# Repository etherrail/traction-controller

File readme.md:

# EtherRail Traction Controller TC1000PX22+D+EA
The WiFi based controller for locomotives and other rolling stock.
This device is a drop in replacement for any DCC boards.

Main Features
- WiFi enabled
- Plux2 Interface according to [NEM 658](./documentation/nem658.pdf)
- Inertia Sensor for speed control (instead of the common power control)
- Sound up to 96kHz
- 1A motor current (3.6A Peak)
- Track power probe
- Low production cost
- Tip over, stall and push detection

Product Code
- `TC` traction controller
- `1000` 1000mA nominal current
- `PX22` PluX22 plugging interface (NEM 658)
- `+D` debugging version (USB compatible, status LEDs)
- `+CA` external antenna

## To Do
- Test Boards (currently in production)
- Add GPIO pins

## Connectivity
The device connects with WiFi or Bluetooth.
An external antenna should be attached.

## Ineria Sensor
Usually, the trains are controlled by setting a motor power level, not a target speed. The IMU sensor integrates an accelerometer and a gyroscope, which can be used to estimate the actual speed of the train.

No more speed calibrations and motor ramps - the controller can automatically compensate for heavier trains or gradients. Stalling can be detect too, both total stalling and wheel-slip, which can then be counter acted with automatically induced power bursts. The controller can detect being pushed too, for example in a collision case. And even a tip over can be detected.

## Track Power Probe
The traction controller constantly measures the track voltage.
When an outage is detected (which usually happens every couple miliseconds, even with clean tracks), the controller goes into sleep mode to preserve energy on the on board capacitor bank.

This can be used to monitor the tracks quality and schedule maintenance before issues arise.

## Sound
The board contains a 3.2W@4Ohm sound chip.

To be tested.

## Function Outputs
600mA per channel.

Warning: The output are directly connected to the P-Channel mosfets, additional protected may be required for some output devices.

## Expandability
The processor used on this device (ESP32C3) is more than capable for this task.
We could add camera functionality with this chip!
DCC emulation is theoretically possible.

The board currently contains a full USB debugging interface (pads only, but a programmer is included on the ESP).

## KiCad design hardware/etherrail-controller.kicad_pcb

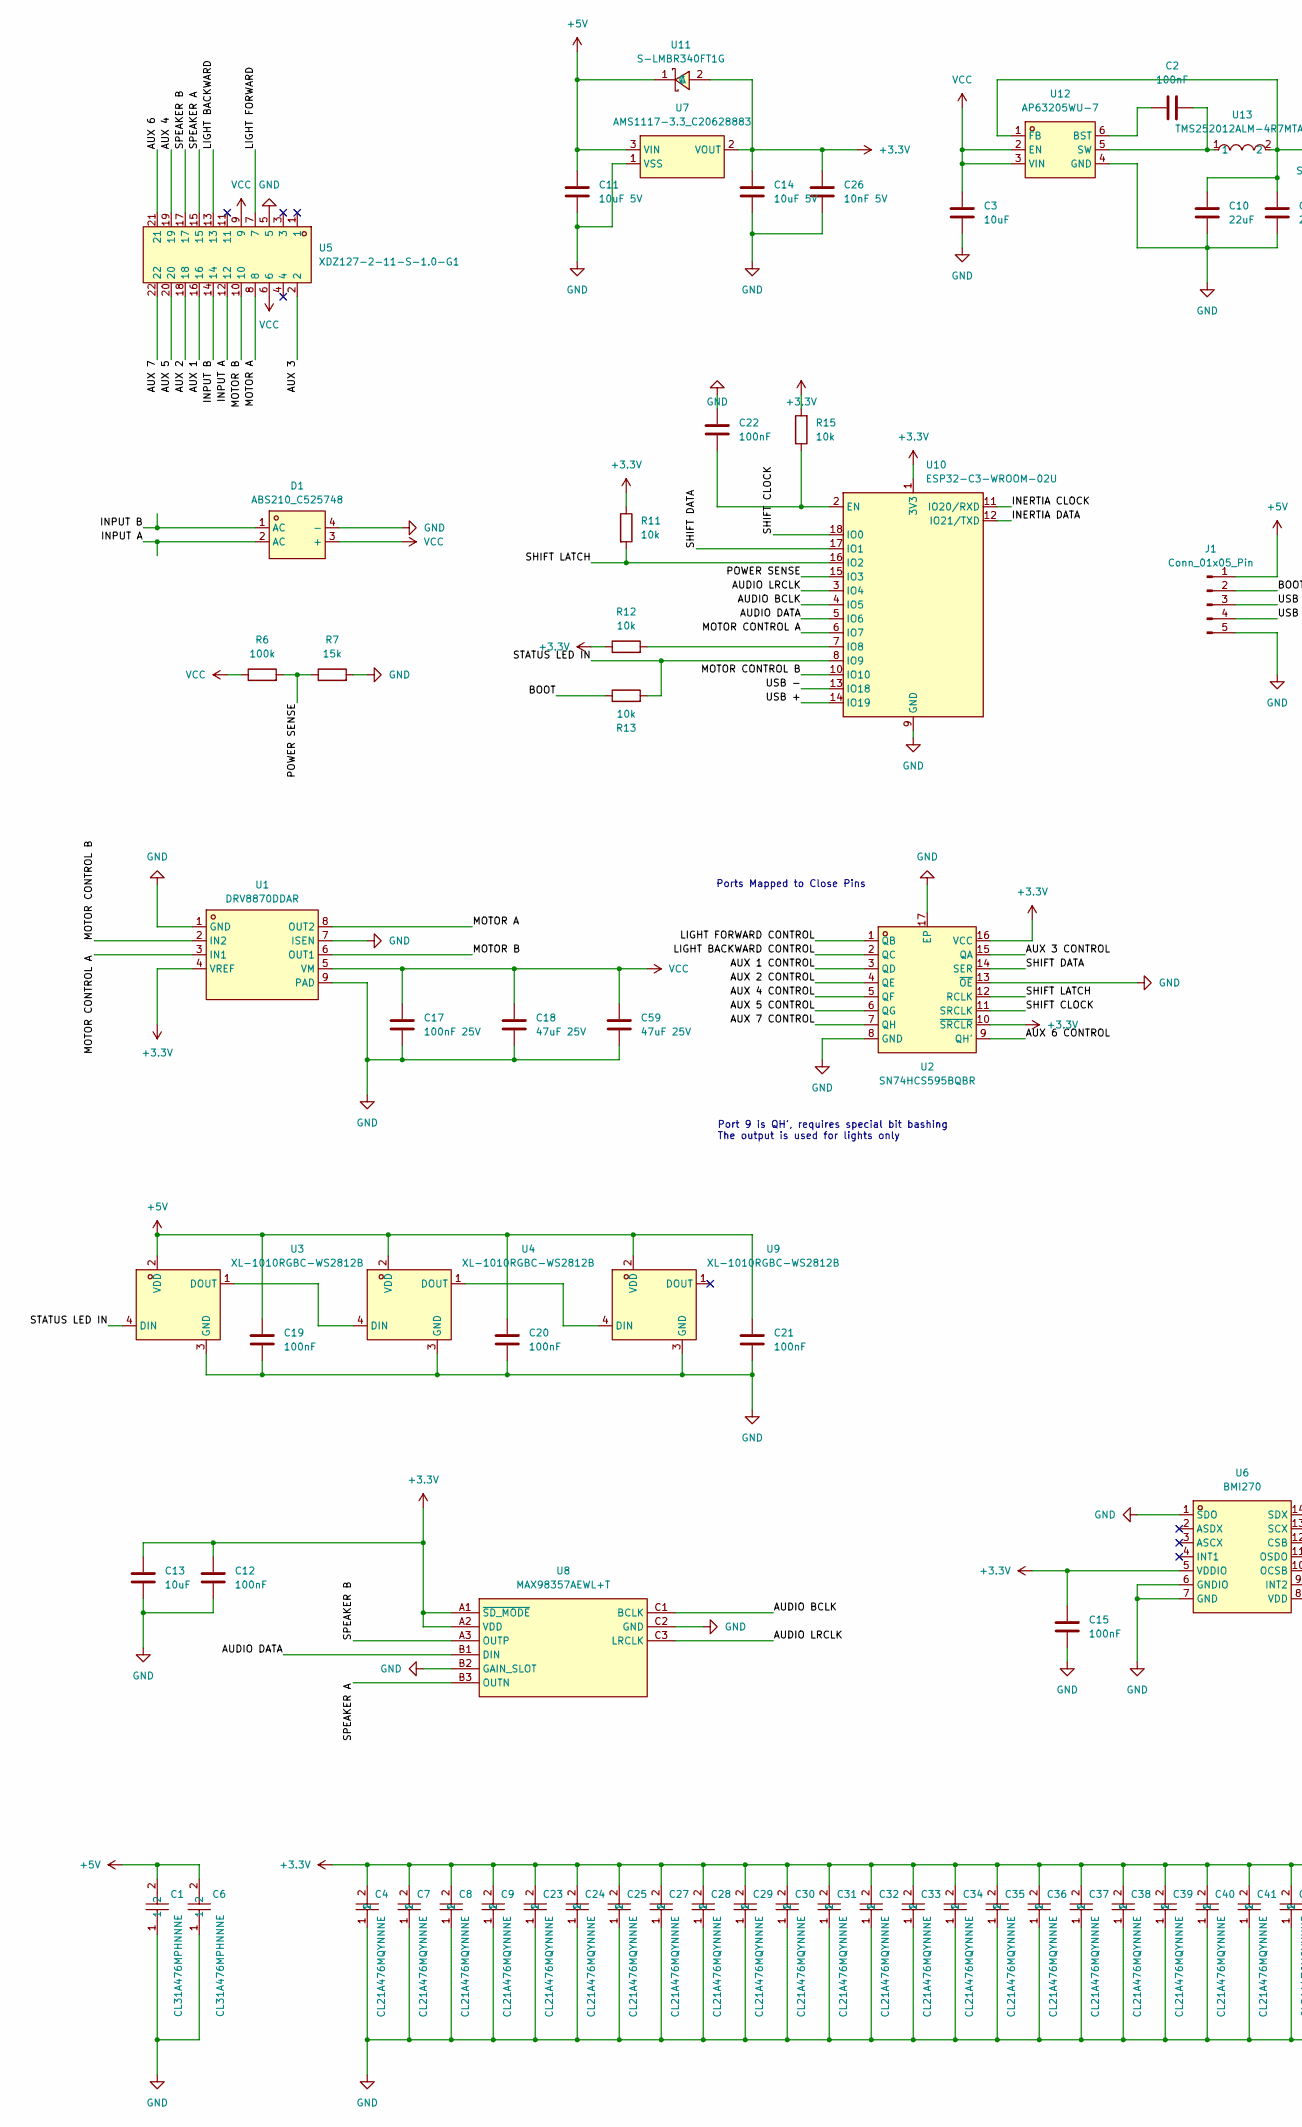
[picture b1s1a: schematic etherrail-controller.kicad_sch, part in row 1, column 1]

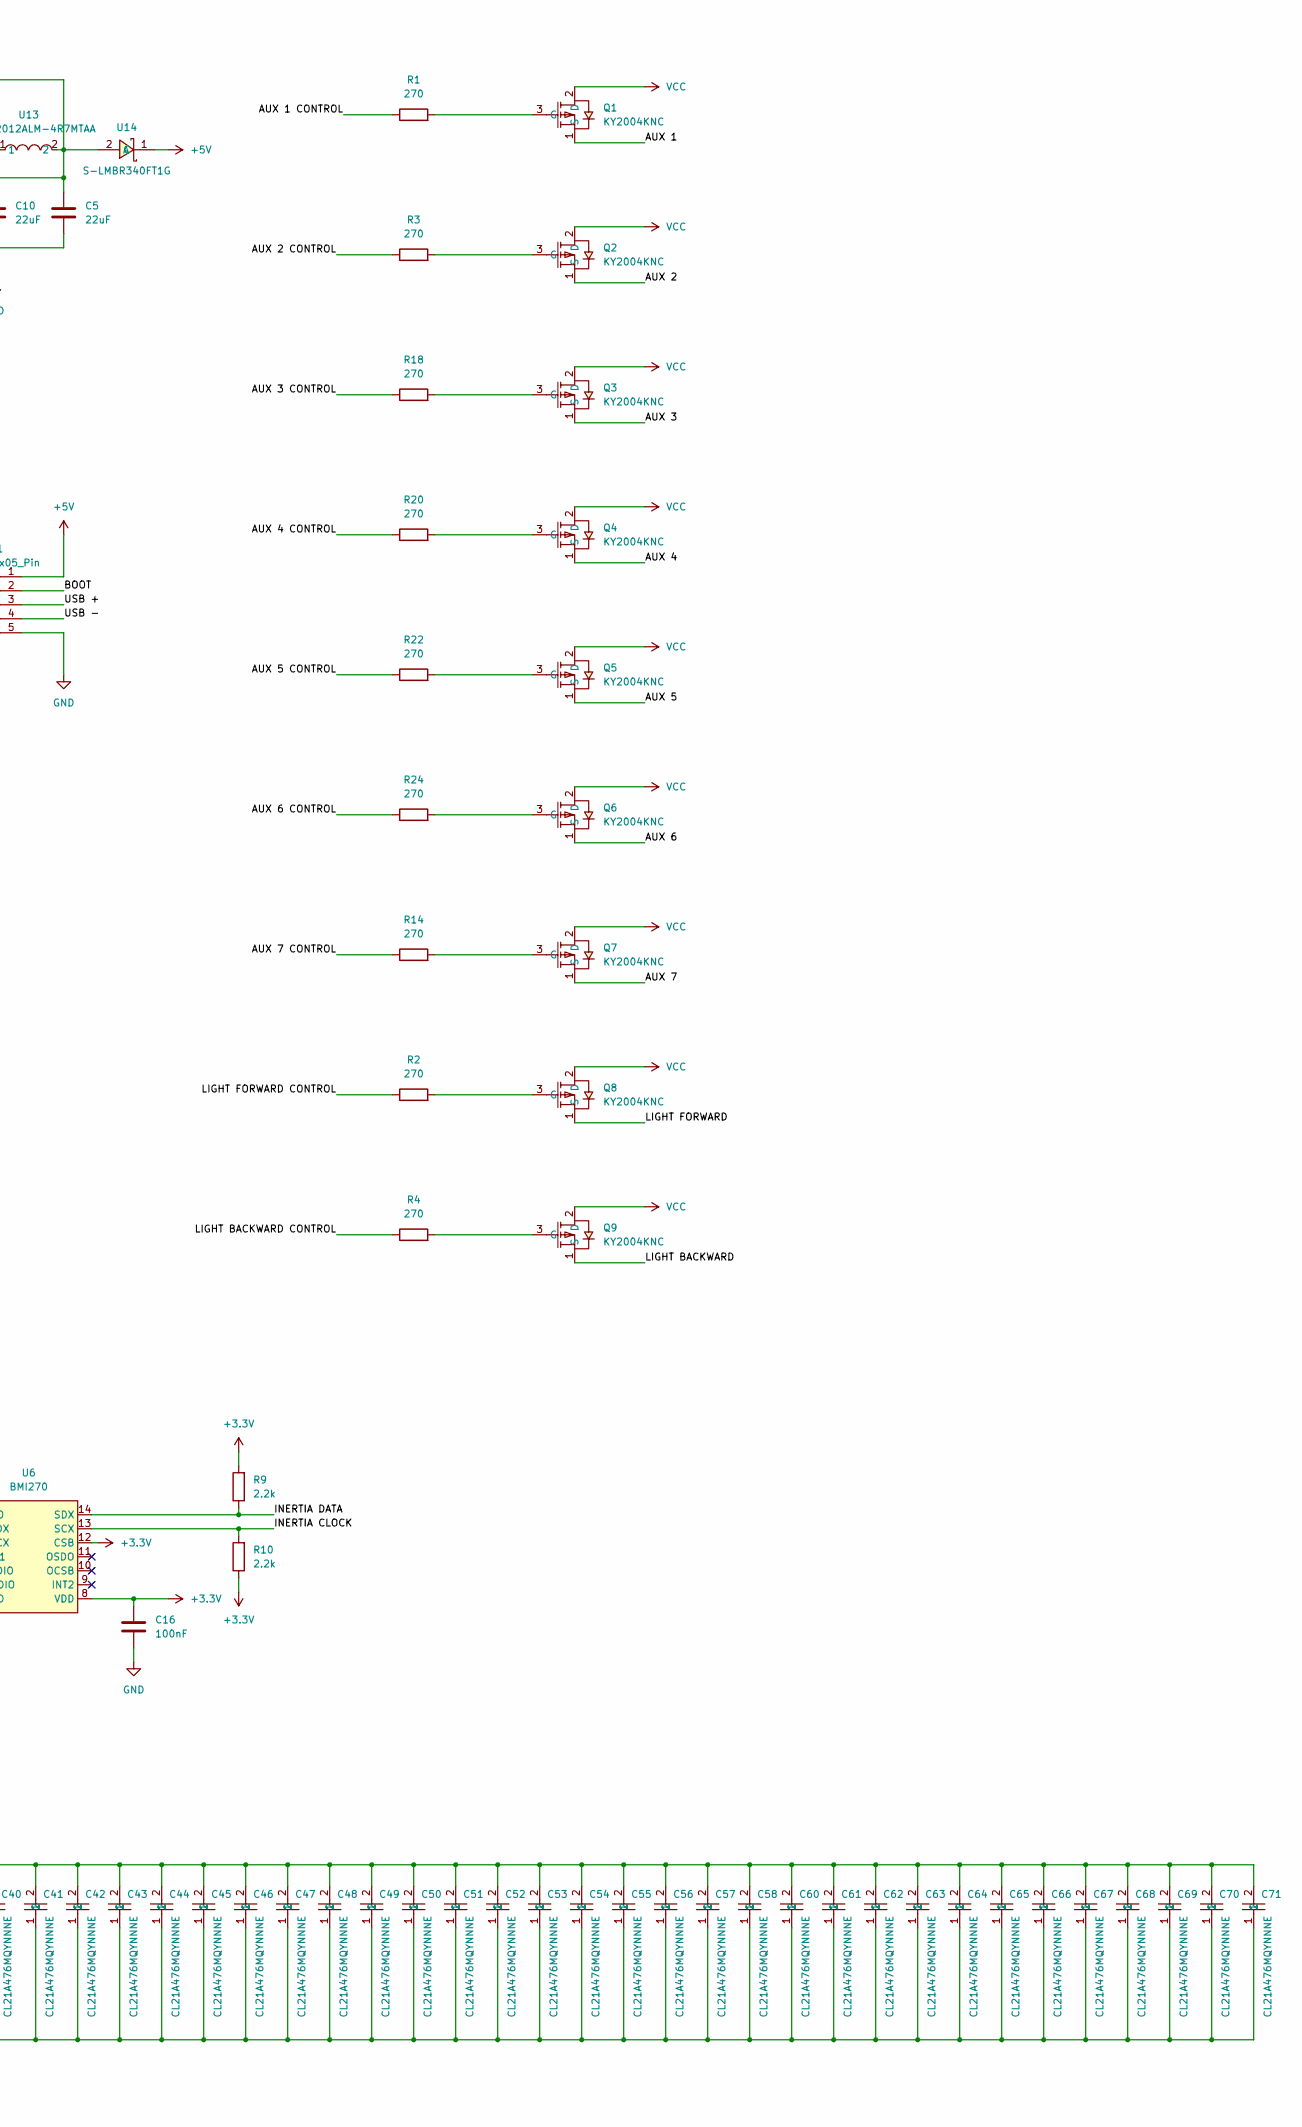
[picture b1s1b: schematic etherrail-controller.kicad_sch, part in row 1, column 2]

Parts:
C1, C6: CL31A476MPHNNNE; C1206; LCSC Part C96123
C2, C22: 100nF; C_0402_1005Metric
C3, C13: 10uF; C_0402_1005Metric
C4, C7, C8, C9, C23, C24, C25, C27, C28, C29, C30, C31, C32, C33, C34, C35, C36, C37, C38, C39, C40, C41, C42, C43, C44, C45, C46, C47, C48, C49, C50, C51, C52, C53, C54, C55, C56, C57, C58, C60, C61, C62, C63, C64, C65, C66, C67, C68, C69, C70, C71: CL21A476MQYNNNE; C0805; LCSC Part C16780
C5, C10: 22uF; C_0402_1005Metric
C11, C14: 10uF 5V; C_0402_1005Metric
C12, C15, C16, C19, C20, C21: 100nF; C_0201_0603Metric
C17: 100nF 25V; C_0402_1005Metric
C18, C59: 47uF 25V; C_1206_3216Metric
C26: 10nF 5V; C_0402_1005Metric
D1: ABS210_C525748; ABS_L5.1-W4.4-P3.35-LS6.4-BL; LCSC Part C525748
J1: Conn_01x05_Pin; DebugPad
Q1, Q2, Q3, Q4, Q5, Q6, Q7, Q8, Q9: KY2004KNC; DFN1006-3L_L1.0-W0.6-BL; LCSC Part C3029285
R1, R2, R4, R24: 270; R_0402_1005Metric
R3, R14, R18, R20, R22: 270; R_0201_0603Metric
R6: 100k; R_0402_1005Metric
R7: 15k; R_0402_1005Metric
R9, R10: 2.2k; R_0201_0603Metric
R11, R13, R15: 10k; R_0402_1005Metric
R12: 10k; R_0201_0603Metric
U1: DRV8870DDAR; HSOP-8_L5.0-W4.0-P1.27-LS6.2-BL-EP; LCSC Part C86590
U2: SN74HCS595BQBR; DQFN-16_L3.5-W2.5-P0.50-BL-EP; LCSC Part C2876392
U3, U4, U9: XL-1010RGBC-WS2812B; LED-SMD_4P-L1.0-W1.0-TL_XL-1010RGBC-WS2812B; LCSC Part C5349953
U5: XDZ127-2-11-S-1.0-G1; HDR-SMD_22P-P1.27-V-M-R2-C11-LS5.5_1; LCSC Part C19268852
U6: BMI270; LGA-14_L3.0-W2.5-P0.50-BR; LCSC Part C2836813
U7: AMS1117-3.3_C20628883; SOT-89-3_L4.5-W2.5-P1.50-LS4.1-BR-1; LCSC Part C20628883
U8: MAX98357AEWL+T; WLP-9_L1.4-W1.3-P0.40-R3-C3-BR; LCSC Part C2682619
U10: ESP32-C3-WROOM-02U
U11, U14: S-LMBR340FT1G; SOD-123FL_L2.7-W1.8-LS3.8-RD; LCSC Part C2972823
U12: AP63205WU-7; TSOT-23-6_L2.9-W1.6-P0.95-LS2.8-BL; LCSC Part C2071056
U13: TMS252012ALM-4R7MTAA; L1008; LCSC Part C5159366

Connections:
+3.3V: C4.2, C7.2, C8.2, C9.2, C12.2, C13.2, C14.2, C15.2, C16.2, C23.2, C24.2, C25.2, C26.2, C27.2, C28.2, C29.2, C30.2, C31.2, C32.2, C33.2, C34.2, C35.2, C36.2, C37.2, C38.2, C39.2, C40.2, C41.2, C42.2, C43.2, C44.2, C45.2, C46.2, C47.2, C48.2, C49.2, C50.2, C51.2, C52.2, C53.2, C54.2, C55.2, C56.2, C57.2, C58.2, C60.2, C61.2, C62.2, C63.2, C64.2, C65.2, C66.2, C67.2, C68.2, C69.2, C70.2, C71.2, R9.2, R10.1, R11.1, R12.1, R15.2, U1.4 (VREF), U2.10 (~SRCLR), U2.16 (VCC), U6.5 (VDDIO), U6.8 (VDD), U6.12 (CSB), U7.2 (VOUT), U8.A1 (~SD_MODE), U8.A2 (VDD), U10.1 (3V3), U11.2 (A)
+5V: C1.2, C6.2, C11.2, C19.2, C20.2, C21.2, J1.1, U3.2 (VDD), U4.2 (VDD), U7.3 (VIN), U9.2 (VDD), U11.1 (C), U14.1 (C)
/AUDIO BCLK: U8.C1 (BCLK), U10.4 (IO5)
/AUDIO DATA: U8.B1 (DIN), U10.5 (IO6)
/AUDIO LRCLK: U8.C3 (LRCLK), U10.3 (IO4)
/AUX 1: Q1.1 (S), U5.16
/AUX 1 CONTROL: R1.1, U2.3 (QD)
/AUX 2: Q2.1 (S), U5.18
/AUX 2 CONTROL: R3.1, U2.4 (QE)
/AUX 3: Q3.1 (S), U5.2
/AUX 3 CONTROL: R18.1, U2.15 (QA)
/AUX 4: Q4.1 (S), U5.19
/AUX 4 CONTROL: R20.1, U2.5 (QF)
/AUX 5: Q5.1 (S), U5.20
/AUX 5 CONTROL: R22.1, U2.6 (QG)
/AUX 6: Q6.1 (S), U5.21
/AUX 6 CONTROL: R24.1, U2.9 (QH')
/AUX 7: Q7.1 (S), U5.22
/AUX 7 CONTROL: R14.1, U2.7 (QH)
/BOOT: J1.2, R13.1
/INERTIA CLOCK: R10.2, U6.13 (SCX), U10.11 (IO20/RXD)
/INERTIA DATA: R9.1, U6.14 (SDX), U10.12 (IO21/TXD)
/INPUT A: D1.2 (AC), U5.12
/INPUT B: D1.1 (AC), U5.14
/LIGHT BACKWARD: Q9.1 (S), U5.13
/LIGHT BACKWARD CONTROL: R4.1, U2.2 (QC)
/LIGHT FORWARD: Q8.1 (S), U5.7
/LIGHT FORWARD CONTROL: R2.1, U2.1 (QB)
/MOTOR A: U1.8 (OUT2), U5.8
/MOTOR B: U1.6 (OUT1), U5.10
/MOTOR CONTROL A: U1.3 (IN1), U10.6 (IO7)
/MOTOR CONTROL B: U1.2 (IN2), U10.10 (IO10)
/POWER SENSE: R6.2, R7.1, U10.15 (IO3)
/SHIFT CLOCK: U2.11 (SRCLK), U10.18 (IO0)
/SHIFT DATA: U2.14 (SER), U10.17 (IO1)
/SHIFT LATCH: R11.2, U2.12 (RCLK), U10.16 (IO2)
/SPEAKER A: U5.15, U8.B3 (OUTN)
/SPEAKER B: U5.17, U8.A3 (OUTP)
/STATUS LED IN: R13.2, U3.4 (DIN), U10.8 (IO9)
/USB +: J1.3, U10.14 (IO19)
/USB -: J1.4, U10.13 (IO18)
GND: C1.1, C3.1, C4.1, C5.1, C6.1, C7.1, C8.1, C9.1, C10.1, C11.1, C12.1, C13.1, C14.1, C15.1, C16.1, C17.1, C18.1, C19.1, C20.1, C21.1, C22.1, C23.1, C24.1, C25.1, C26.1, C27.1, C28.1, C29.1, C30.1, C31.1, C32.1, C33.1, C34.1, C35.1, C36.1, C37.1, C38.1, C39.1, C40.1, C41.1, C42.1, C43.1, C44.1, C45.1, C46.1, C47.1, C48.1, C49.1, C50.1, C51.1, C52.1, C53.1, C54.1, C55.1, C56.1, C57.1, C58.1, C59.1, C60.1, C61.1, C62.1, C63.1, C64.1, C65.1, C66.1, C67.1, C68.1, C69.1, C70.1, C71.1, D1.4 (-), J1.5, R7.2, U1.1 (GND), U1.7 (ISEN), U1.9 (PAD), U2.8 (GND), U2.13 (~OE), U2.17 (EP), U3.3 (GND), U4.3 (GND), U5.5, U6.1 (SDO), U6.6 (GNDIO), U6.7 (GND), U7.1 (VSS), U8.B2 (GAIN_SLOT), U8.C2 (GND), U9.3 (GND), U10.9 (GND), U10.19 (GND), U12.4 (GND)
unnamed: Q1.3 (G), R1.2
unnamed: Q2.3 (G), R3.2
unnamed: Q3.3 (G), R18.2
unnamed: Q4.3 (G), R20.2
unnamed: Q5.3 (G), R22.2
unnamed: Q6.3 (G), R24.2
unnamed: Q7.3 (G), R14.2
unnamed: Q8.3 (G), R2.2
unnamed: Q9.3 (G), R4.2
unnamed: U3.1 (DOUT), U4.4 (DIN)
unnamed: U4.1 (DOUT), U9.4 (DIN)
unnamed: C22.2, R15.1, U10.2 (EN)
unnamed: R12.2, U10.7 (IO8)
unnamed: C2.1, U12.6 (BST)
unnamed: C5.2, C10.2, U12.1 (FB), U13.2, U14.2 (A)
unnamed: C2.2, U12.5 (SW), U13.1
VCC: C3.2, C17.2, C18.2, C59.2, D1.3 (+), Q1.2 (D), Q2.2 (D), Q3.2 (D), Q4.2 (D), Q5.2 (D), Q6.2 (D), Q7.2 (D), Q8.2 (D), Q9.2 (D), R6.1, U1.5 (VM), U5.6, U5.9, U12.2 (EN), U12.3 (VIN)

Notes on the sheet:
Ports Mapped to Close Pins
Port 9 is QH', requires special bit bashing The output is used for lights only

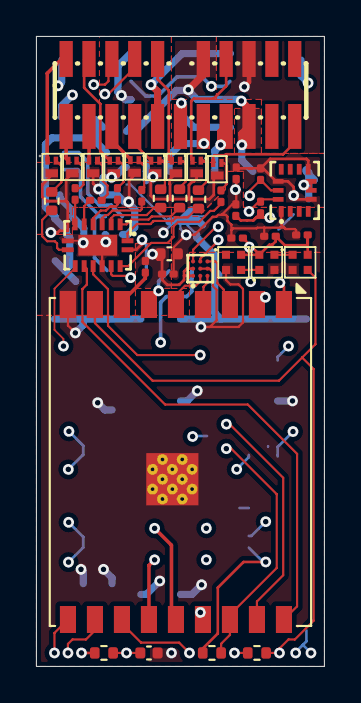
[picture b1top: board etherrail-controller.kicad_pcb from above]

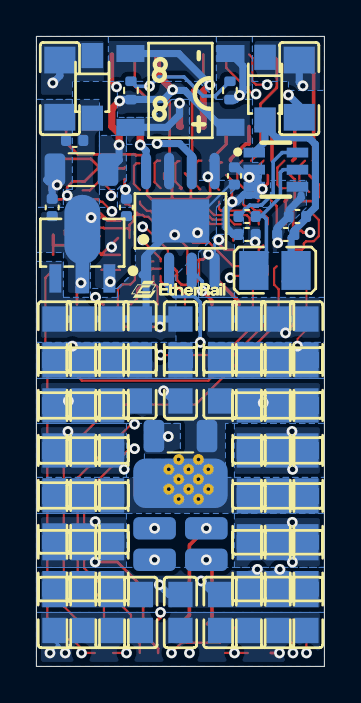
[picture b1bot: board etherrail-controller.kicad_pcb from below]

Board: 6 copper layers, 16.0 x 35.0 mm, 113 parts (73 on the bottom side), 59 nets.

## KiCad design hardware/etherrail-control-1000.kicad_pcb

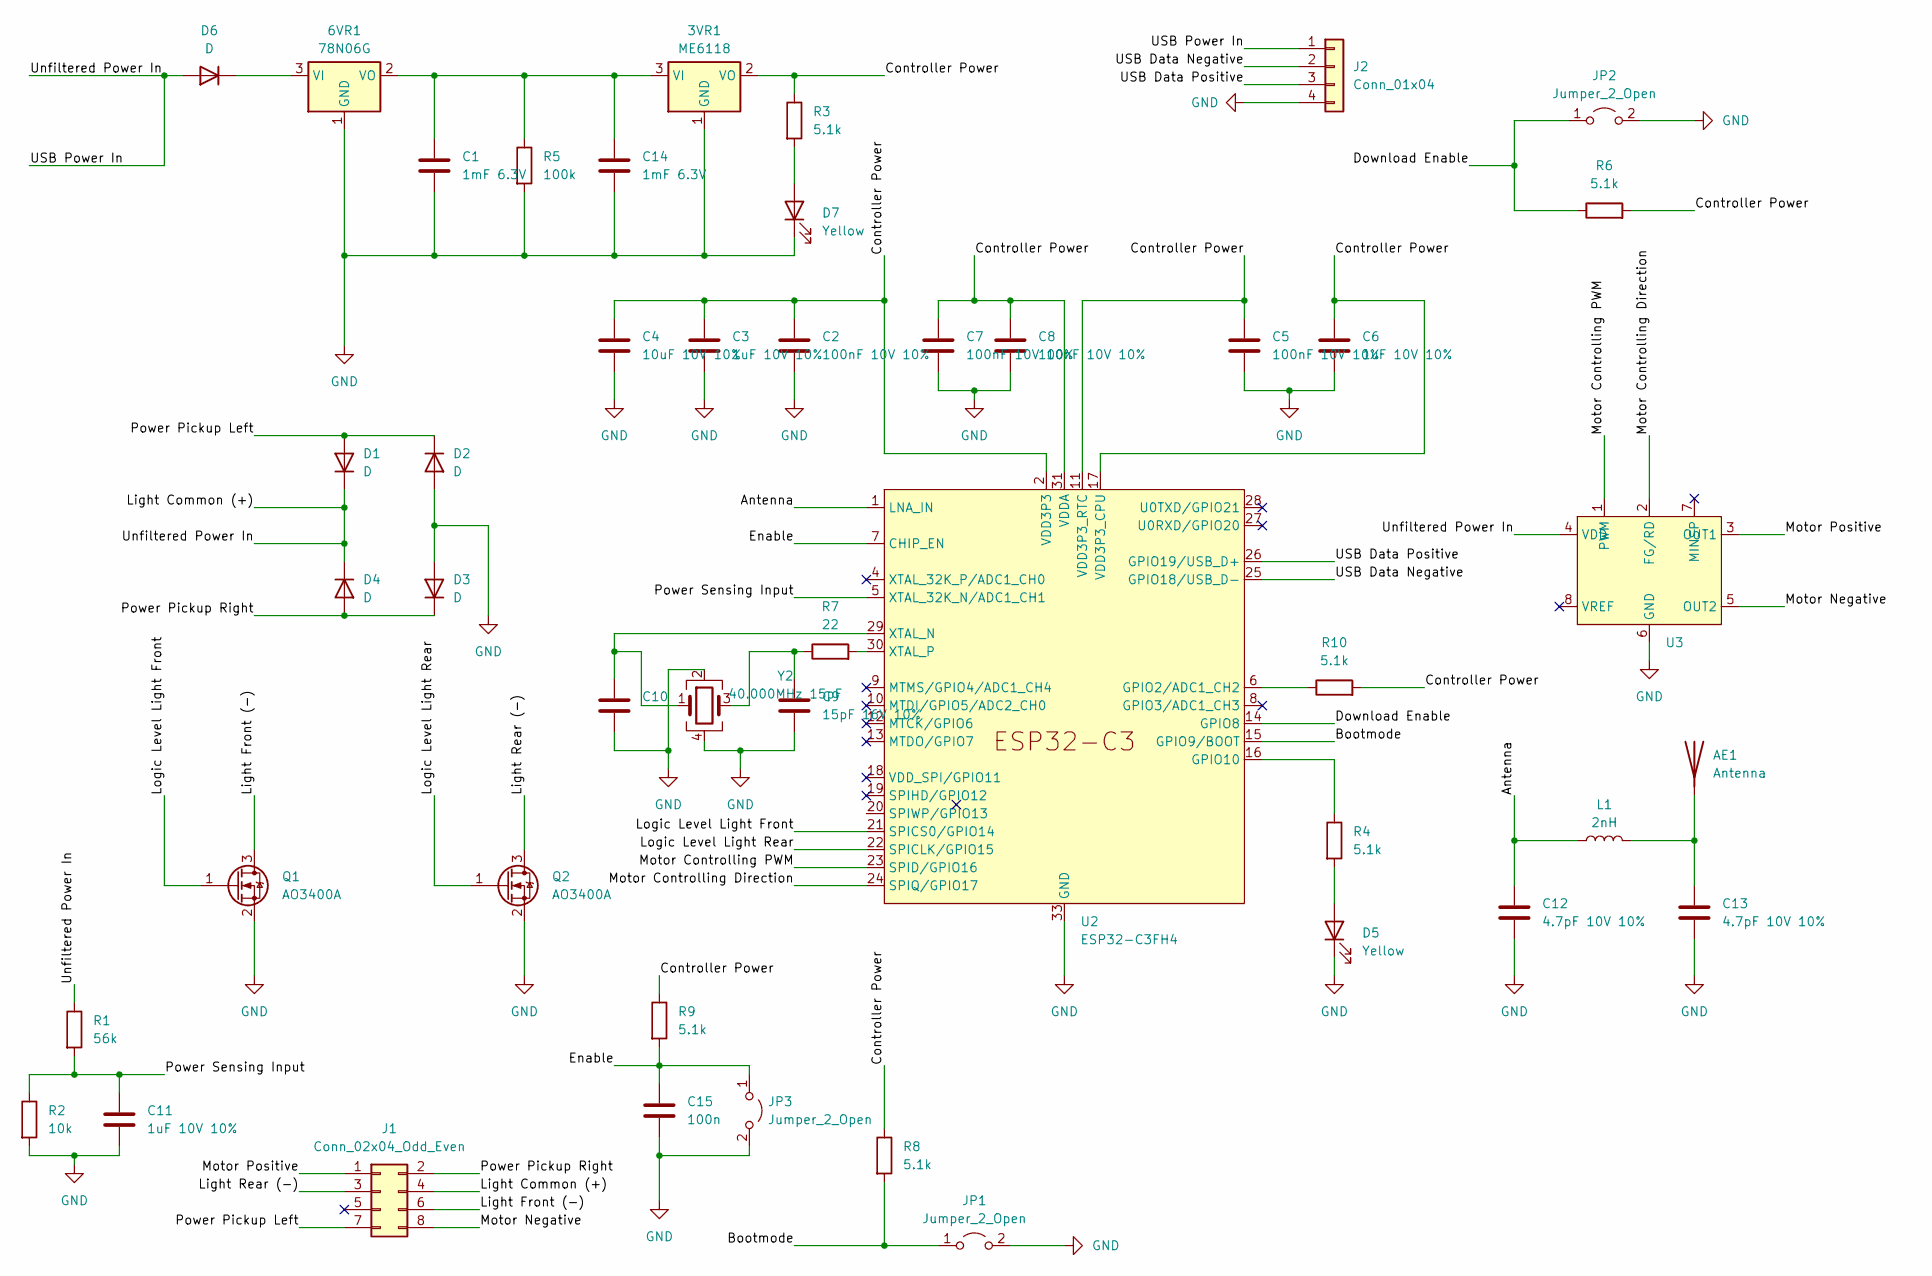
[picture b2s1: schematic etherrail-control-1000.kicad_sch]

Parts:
3VR1: ME6118; SOT-89-3; LCSC C2683411
6VR1: 78N06G; SOT-89-3; LCSC C84863
AE1: Antenna; Yaego ANT8010LL04R2400A
C1, C14: 1mF 6.3V; CP_EIA-7343-43_Kemet-X; LCSC C696799
C2, C5, C7, C8: 100nF 10V 10%; C_0201_0603Metric
C3, C6, C11: 1uF 10V 10%; C_0201_0603Metric
C4: 10uF 10V 10%; C_0402_1005Metric
C9, C10: 15pF 16V 10%; C_0201_0603Metric
C12, C13: 4.7pF 10V 10%; C_0201_0603Metric
C15: 100n; C_0201_0603Metric
D1, D2, D3, D4, D6: D; D_SOD-323
D5, D7: Yellow; LED_0603_1608Metric; LCSC C19171392
J1: Conn_02x04_Odd_Even; PinHeader_2x04_P2.54mm_Vertical
J2: Conn_01x04; PinHeader_1x04_P1.27mm_Vertical
JP1, JP2, JP3: Jumper_2_Open; SolderJumper-2_P1.3mm_Open_Pad1.0x1.5mm
L1: 2nH; L_0201_0603Metric
Q1, Q2: AO3400A; SOT-23
R1: 56k; R_0201_0603Metric
R2: 10k; R_0201_0603Metric
R3, R4, R6, R8, R9, R10: 5.1k; R_0201_0603Metric
R5: 100k; R_0402_1005Metric
R7: 22; R_0201_0603Metric
U2: ESP32-C3FH4; QFN-32-1EP_5x5mm_P0.5mm_EP3.1x3.1mm; LCSC C2858491
U3: DFN-8-1EP_3x3mm_P0.65mm_EP1.55x2.4mm; LCSC C2832995
Y2: 40.000MHz 15pF; Crystal_SMD_3225-4Pin_3.2x2.5mm; LCSC Part C9010

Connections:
/Antenna: C12.1, L1.1, U2.1 (LNA_IN)
/Bootmode: JP1.1 (A), R8.2, U2.15 (GPIO9/BOOT)
/Controller Power: 3VR1.2 (VO), C2.1, C3.1, C4.1, C5.1, C6.1, C7.1, C8.1, R3.1, R6.2, R8.1, R9.1, R10.2, U2.2 (VDD3P3), U2.3 (VDD3P3), U2.11 (VDD3P3_RTC), U2.17 (VDD3P3_CPU), U2.31 (VDDA), U2.32 (VDDA)
/Download Enable: JP2.1 (A), R6.1, U2.14 (GPIO8)
/Enable: C15.1, JP3.1 (A), R9.2, U2.7 (CHIP_EN)
/Light Common (+): D1.1 (K), D4.1 (K), D6.2 (A), J1.4, J2.1, R1.1, U3.4 (VDD)
/Light Front (-): J1.6, Q1.3 (D)
/Light Rear (-): J1.3, Q2.3 (D)
/Logic Level Light Front: Q1.1 (G), U2.21 (SPICS0/GPIO14)
/Logic Level Light Rear: Q2.1 (G), U2.22 (SPICLK/GPIO15)
/Motor Controlling Direction: U2.24 (SPIQ/GPIO17), U3.2 (FG/RD)
/Motor Controlling PWM: U2.23 (SPID/GPIO16), U3.1 (PWM)
/Motor Negative: J1.8, U3.5 (OUT2)
/Motor Positive: J1.1, U3.3 (OUT1)
/Power Pickup Left: D1.2 (A), D2.1 (K), J1.7
/Power Pickup Right: D3.1 (K), D4.2 (A), J1.2
/Power Sensing Input: C11.1, R1.2, R2.1, U2.5 (XTAL_32K_N/ADC1_CH1)
/USB Data Negative: J2.2, U2.25 (GPIO18/USB_D-)
/USB Data Positive: J2.3, U2.26 (GPIO19/USB_D+)
GND: 3VR1.1 (GND), 6VR1.1 (GND), C1.2, C2.2, C3.2, C4.2, C5.2, C6.2, C7.2, C8.2, C9.2, C10.2, C11.2, C12.2, C13.2, C14.2, C15.2, D2.2 (A), D3.2 (A), D5.1 (K), D7.1 (K), J2.4, JP1.2 (B), JP2.2 (B), JP3.2 (B), Q1.2 (S), Q2.2 (S), R2.2, R5.2, U2.33 (GND), U3.6 (GND), Y2.2, Y2.4
unnamed: 3VR1.3 (VI), 6VR1.2 (VO), C1.1, C14.1, R5.1
unnamed: 6VR1.3 (VI), D6.1 (K)
unnamed: AE1.1 (A), C13.1, L1.2
unnamed: C9.1, R7.1, Y2.3
unnamed: D5.2 (A), R4.2
unnamed: D7.2 (A), R3.2
unnamed: R10.1, U2.6 (GPIO2/ADC1_CH2)
unnamed: R4.1, U2.16 (GPIO10)
unnamed: C10.1, U2.29 (XTAL_N), Y2.1
unnamed: R7.2, U2.30 (XTAL_P)

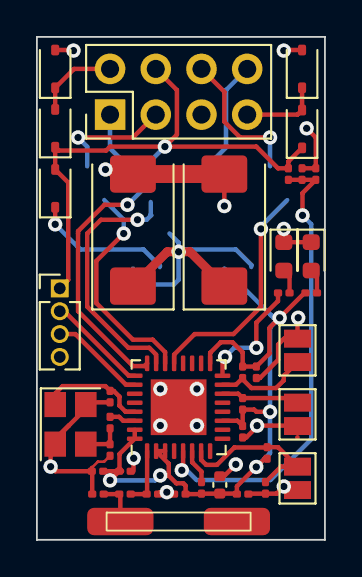
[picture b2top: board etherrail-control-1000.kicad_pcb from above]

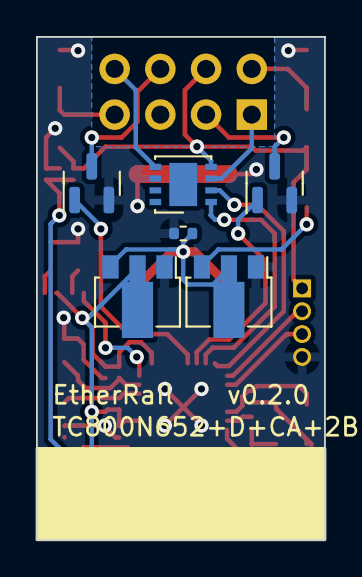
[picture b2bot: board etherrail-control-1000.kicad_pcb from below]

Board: 2 copper layers, 16.0 x 27.9 mm, 46 parts (6 on the bottom side), 30 nets.

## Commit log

2023-11-12 Add PCB
2023-11-13 Fix 10uF cap footprint
2023-11-13 Fix remove non-source files
2023-11-13 Fix remove kicad symbols
2023-11-13 Fix remove lock file
2023-11-13 Add basic readme
2023-11-13 Add board area comment
2023-11-13 Add 0402 10uF filter cap to board
2023-11-13 Fix input rectifier ground track power rating
2023-11-13 Fix missing crystal speed property
2023-11-15 Add NEM 652 note
2023-11-15 Fix remove duplicate file
2023-11-15 Add nem652 documentation archive
2023-12-10 Add protocol documentation
2024-01-13 WIP: Add revised hardware
2024-01-13 Fix rename product
2024-01-15 Add EN jumper
2024-01-15 Add GPIO2 rotue
2024-01-15 Fix use ESP32-C3 with flash (C3-FH4)
2024-01-20 Fix connected paths
2025-04-28 Add rewised board with IMU, capacitor bank, PluX22 interface and sound.
